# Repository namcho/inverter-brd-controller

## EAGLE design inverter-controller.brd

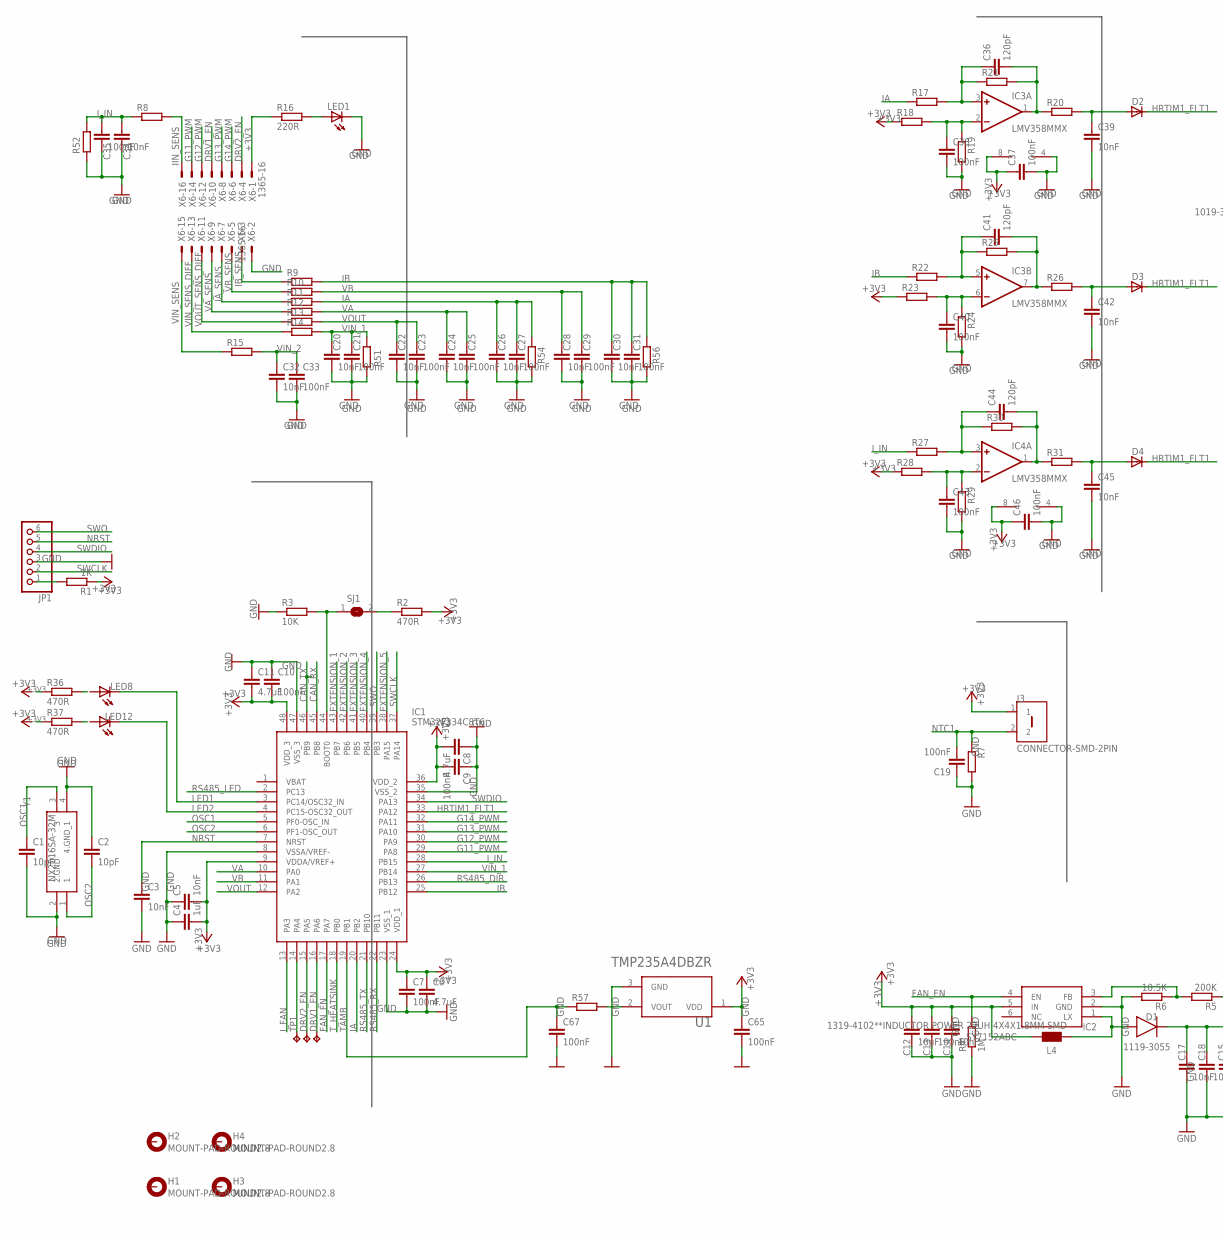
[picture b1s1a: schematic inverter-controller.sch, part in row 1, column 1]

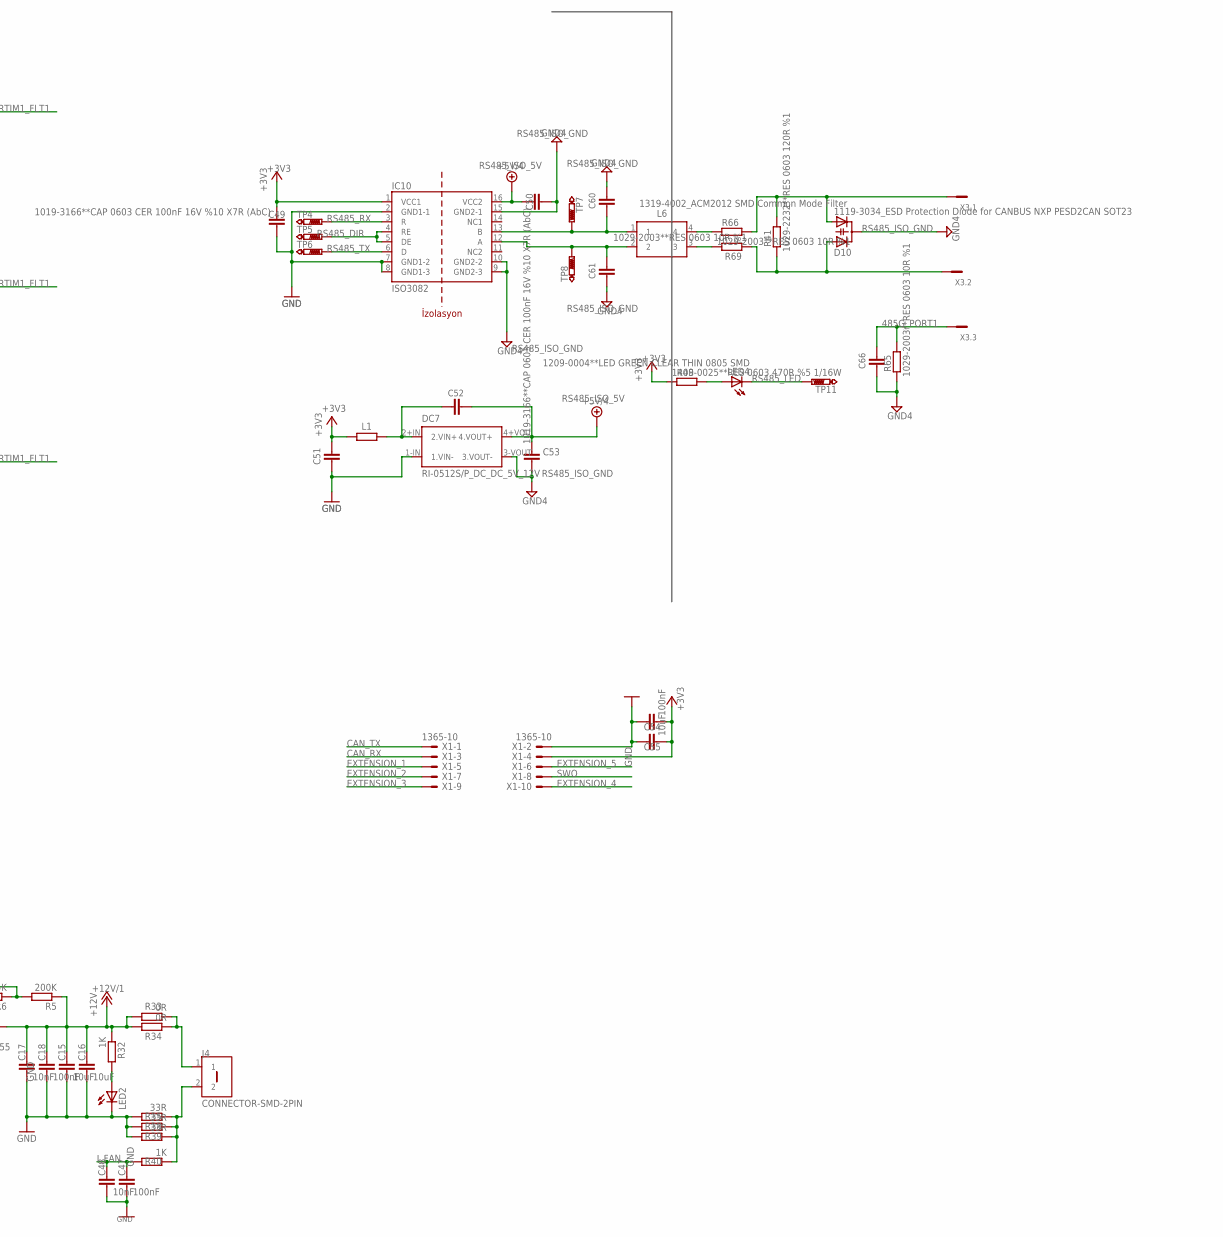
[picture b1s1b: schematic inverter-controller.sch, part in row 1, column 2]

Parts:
C1, C2: 10pF; C0603_ENKO
C3, C5, C14, C17, C20, C22, C24, C26, C28, C30, C32, C34, C39, C42, C45, C48: 10nF; C0603_ENKO
C4: 1uF; C0603_ENKO
C6, C8, C11: 4.7uF; C0603_ENKO
C7, C9, C10, C13, C18, C19, C21, C23, C25, C27, C29, C31, C33, C35, C37, C38, C40, C43, C46, C47, C54, C65, C67: 100nF; C0603_ENKO
C12, C15, C16, C55: 10uF; C0603_ENKO
C36, C41, C44: 120pF; C0603_ENKO
C49, C50: 1019-3166**CAP 0603 CER 100nF 16V %10 X7R (AbC); C0603
C51, C53: 1019-3168","CAP 0805 CER 2.2uF 16V %10 X7R (AbC); C0805
C52: 0019-3020","CAP TH CER 470pF 3kV Y5P %10 85C F=7.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; C050-055X075
C60, C61: 1200920378**CAP 0603 CER 100p 50V%5 NP0; C0603
C66: NC; C0603
D1: 1119-3055; DIOM5226X290N
D2, D3, D4: DIODE-SOD80C; SOD80C
D10: 1119-3034_ESD Protection Diode for CANBUS NXP PES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; SOT23
DC7: RI-0512S/P_DC_DC_5V_12V
H1, H2, H3, H4: MOUNT-PAD-ROUND2.8; 2,8-PAD
IC1: STM32F334C8T6; QFP50P900X900X160-48N
IC2: SY7152ABC; SOT95P285X140-6N
IC3, IC4: LMV358MMX; MSOP08
IC10: ISO3082
J3, J4: CONNECTOR-SMD-2PIN
JP1: PINHD-1X6; 1X06
L1: 1319-4025","INDUCTOR SMD 0805 4.7uH 500mA CL2012C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; R0805
L4: 1319-4102**INDUCTOR POWER 22UH 4X4X1.8MM SMD; WE-PD2_S
L6: 1319-4002_ACM2012 SMD Common Mode Filter; ACM2012-900--2P-T002
LED1, LED2: LEDCHIP-LED0805; CHIP-LED0805
LED4: 1209-0004**LED GREEN CLEAR THIN 0805 SMD; CHIP-LED0805
LED8, LED12: LEDCHIPLED_0805; CHIPLED_0805
R1, R32, R40: 1K; R0603_ENKO
R2, R36, R37: 470R; R0603_ENKO
R3: 10K; R0603_ENKO
R4: 1M; R0603_ENKO
R5: 200K; R0603_ENKO
R6: 10.5K; R0603_ENKO
R7, R8, R9, R10, R11, R12, R13, R14, R15, R17, R18, R19, R20, R21, R22, R23, R24, R25, R26, R27, R28, R29, R30, R31, R51, R52, R54, R56, R57: R-EU_R0603E; R0603_ENKO
R16: 220R; R0603_ENKO
R33, R34: 0R; R0603_ENKO
R35, R38, R39: 33R; R0603_ENKO
R41: 1029-2232**RES 0603 120R %1; R0603
R48: 1409-0025**RES 0603 470R %5 1/16W; R0603
R65, R66, R69: 1029-2003**RES 0603 10R %1; R0603
SJ1: SJ
TP1, TP2, TP3: TPB1,27; B1,27
TP4, TP5, TP6, TP7, TP8, TP11: PTR1TP18R; TP18R
U1: MCP9701; TEXAS_INSTRUMENTS_TMP235A4DBZR_3
X1: 1365-10
X3: 0289-9068**15EDGVC-3.81-03P-14; MCV3
X6: 1365-16
Y1: NX2016SA-32M

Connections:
485A_PORT: D10.1 (A1), R41.1, R69.1, X3.2
485B_PORT: D10.2 (A2), R41.2, R66.2, X3.1
485G_PORT1: C66.1, R65.2, X3.3
+3V3: C4.2, C5.2, C6.1, C7.1, C8.2, C9.2, C10.2, C11.2, C12.1, C13.1, C14.1, C37.1, C46.1, C49.2, C51.1, C54.2, C55.2, C65.1, IC1.9 (VDDA/VREF+), IC1.24 (VDD_1), IC1.36 (VDD_2), IC1.48 (VDD_3), IC2.5 (IN), IC3.8 (V+), IC4.8 (V+), IC10.1 (VCC1), J3.1, L1.1, L4.1 (2), R1.1, R2.2, R16.1, R18.1, R23.1, R28.1, R36.1, R37.1, R48.1, U1.1 (VDD), X1.4, X6.1
+12V/1: C15.1, C16.1, C17.1, C18.1, D1.1 (C), R5.1, R32.1, R33.2, R34.2
CAN_RX: IC1.45 (PB8), X1.3
CAN_TX: IC1.46 (PB9), X1.1
DRV1_EN: IC1.16 (PA6), TP3.TP, X6.10
DRV2_EN: IC1.15 (PA5), TP2.TP, X6.4
EXTENSION_1: IC1.43 (PB7), X1.5
EXTENSION_2: IC1.42 (PB6), X1.7
EXTENSION_3: IC1.41 (PB5), X1.9
EXTENSION_4: IC1.40 (PB4), X1.10
EXTENSION_5: IC1.38 (PA15), X1.6
FAN_EN: IC1.17 (PA7), IC2.4 (EN), R4.2
G11_PWM: IC1.29 (PA8), X6.14
G12_PWM: IC1.30 (PA9), X6.12
G13_PWM: IC1.31 (PA10), X6.8
G14_PWM: IC1.32 (PA11), X6.6
GND: C1.2, C2.1, C3.2, C4.1, C5.1, C6.2, C7.2, C8.1, C9.1, C10.1, C11.1, C12.2, C13.2, C14.2, C15.2, C16.2, C17.2, C18.2, C19.1, C20.2, C21.2, C22.2, C23.2, C24.2, C25.2, C26.2, C27.2, C28.2, C29.2, C30.2, C31.2, C32.2, C33.2, C34.2, C35.2, C37.2, C38.2, C39.2, C40.2, C42.2, C43.2, C45.2, C46.2, C47.2, C48.2, C49.1, C51.2, C54.1, C55.1, C65.2, C67.2, DC7.1-IN (1.VIN-), IC1.8 (VSSA/VREF-), IC1.23 (VSS_1), IC1.35 (VSS_2), IC1.47 (VSS_3), IC2.2 (GND), IC3.4 (V-), IC4.4 (V-), IC10.2 (GND1-1), IC10.7 (GND1-2), IC10.8 (GND1-3), JP1.3, LED1.C, LED2.C, R3.1, R4.1, R6.2, R7.2, R19.2, R24.2, R29.2, R35.2, R38.2, R39.2, R51.1, R52.1, R54.1, R56.1, U1.3 (GND), X1.2, X6.2, Y1.2 (2.GND), Y1.4 (4.GND_1)
HRTIM1_FLT1: D2.C, D3.C, D4.C, IC1.33 (PA12)
IA: C26.1, C27.1, IC1.20 (PB2), R11.2, R17.1, R54.2
IA_SENS: R11.1, X6.7
IB: C30.1, C31.1, IC1.25 (PB12), R9.2, R22.1, R56.2
IB_SENS: R9.1, X6.3
IIN_SENS: R8.2, X6.16
I_FAN: C47.1, C48.1, IC1.13 (PA3), R40.2
I_IN: C34.1, C35.1, IC1.28 (PB15), R8.1, R27.1, R52.2
LED1: IC1.3 (PC14/OSC32_IN), LED8.C
LED2: IC1.4 (PC15-OSC32_OUT), LED12.C
unnamed: C36.2, IC3.1 (OUT), R20.1, R21.2
unnamed: R2.1, SJ1.2
unnamed: IC1.14 (PA4), TP1.TP
unnamed: IC1.44 (BOOT0), R3.2, SJ1.1
unnamed: C36.1, IC3.3 (+IN), R17.2, R21.1
unnamed: IC2.3 (FB), R5.2, R6.1
unnamed: LED2.A, R32.2
unnamed: J4.2, R35.1, R38.1, R39.1, R40.1
unnamed: D1.2 (A), IC2.1 (LX), L4.2 (1)
unnamed: C39.1, D2.A, R20.2
unnamed: C42.1, D3.A, R26.2
unnamed: C38.1, IC3.2 (-IN), R18.2, R19.1
unnamed: C41.1, IC3.5 (+IN), R22.2, R25.1
unnamed: C44.1, IC4.3 (+IN), R27.2, R30.1
unnamed: C40.1, IC3.6 (-IN), R23.2, R24.1
unnamed: C41.2, IC3.7 (OUT), R25.2, R26.1
unnamed: C45.1, D4.A, R31.2
unnamed: C43.1, IC4.2 (-IN), R28.2, R29.1
unnamed: LED1.A, R16.2
unnamed: C44.2, IC4.1 (OUT), R30.2, R31.1
unnamed: LED4.A, R48.2
unnamed: JP1.1, R1.2
unnamed: J4.1, R33.1, R34.1
unnamed: LED8.A, R36.2
unnamed: C61.1, IC10.12 (A), L6.2, TP8.TP
unnamed: L6.4, R66.1
unnamed: R57.2, U1.2 (VOUT)
unnamed: LED12.A, R37.2
unnamed: L6.3, R69.2
unnamed: C60.2, IC10.13 (B), L6.1, TP7.TP
unnamed: C52.1, DC7.2+IN (2.VIN+), L1.2
NRST: C3.1, IC1.7 (NRST), JP1.5
NTC1: C19.2, J3.2, R7.1
OSC1: C1.1, IC1.5 (PF0-OSC_IN), Y1.3
OSC2: C2.2, IC1.6 (PF1-OSC_OUT), Y1.1
RS485_DIR: IC1.26 (PB13), IC10.4 (RE), IC10.5 (DE), TP5.TP
RS485_ISO_5V: C50.2, C52.2, C53.1, DC7.4+VOU (4.VOUT+), IC10.16 (VCC2)
RS485_ISO_GND: C50.1, C53.2, C60.1, C61.2, C66.2, D10.3 (C), DC7.3-VOUT (3.VOUT-), IC10.9 (GND2-3), IC10.10 (GND2-2), IC10.15 (GND2-1), R65.1
RS485_LED: IC1.2 (PC13), LED4.C, TP11.TP
RS485_RX: IC1.22 (PB11), IC10.3 (R), TP4.TP
RS485_TX: IC1.21 (PB10), IC10.6 (D), TP6.TP
SWCLK: IC1.37 (PA14), JP1.2
SWDIO: IC1.34 (PA13), JP1.4
SWO: IC1.39 (PB3), JP1.6, X1.8
TAMB: C67.1, IC1.19 (PB1), R57.1
T_HEATSINK: IC1.18 (PB0)
VA: C24.1, C25.1, IC1.10 (PA0), R12.2
VA_SENS: R12.1, X6.9
VB: C28.1, C29.1, IC1.11 (PA1), R10.2
VB_SENS: R10.1, X6.5
VIN_1: C20.1, C21.1, IC1.27 (PB14), R14.2, R51.2
VIN_2: C32.1, C33.1, R15.2
VIN_SENS: R15.1, X6.15
VIN_SENS_DIFF: R14.1, X6.13
VOUT: C22.1, C23.1, IC1.12 (PA2), R13.2
VOUT_SENS_DIFF: R13.1, X6.11

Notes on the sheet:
İzolasyon

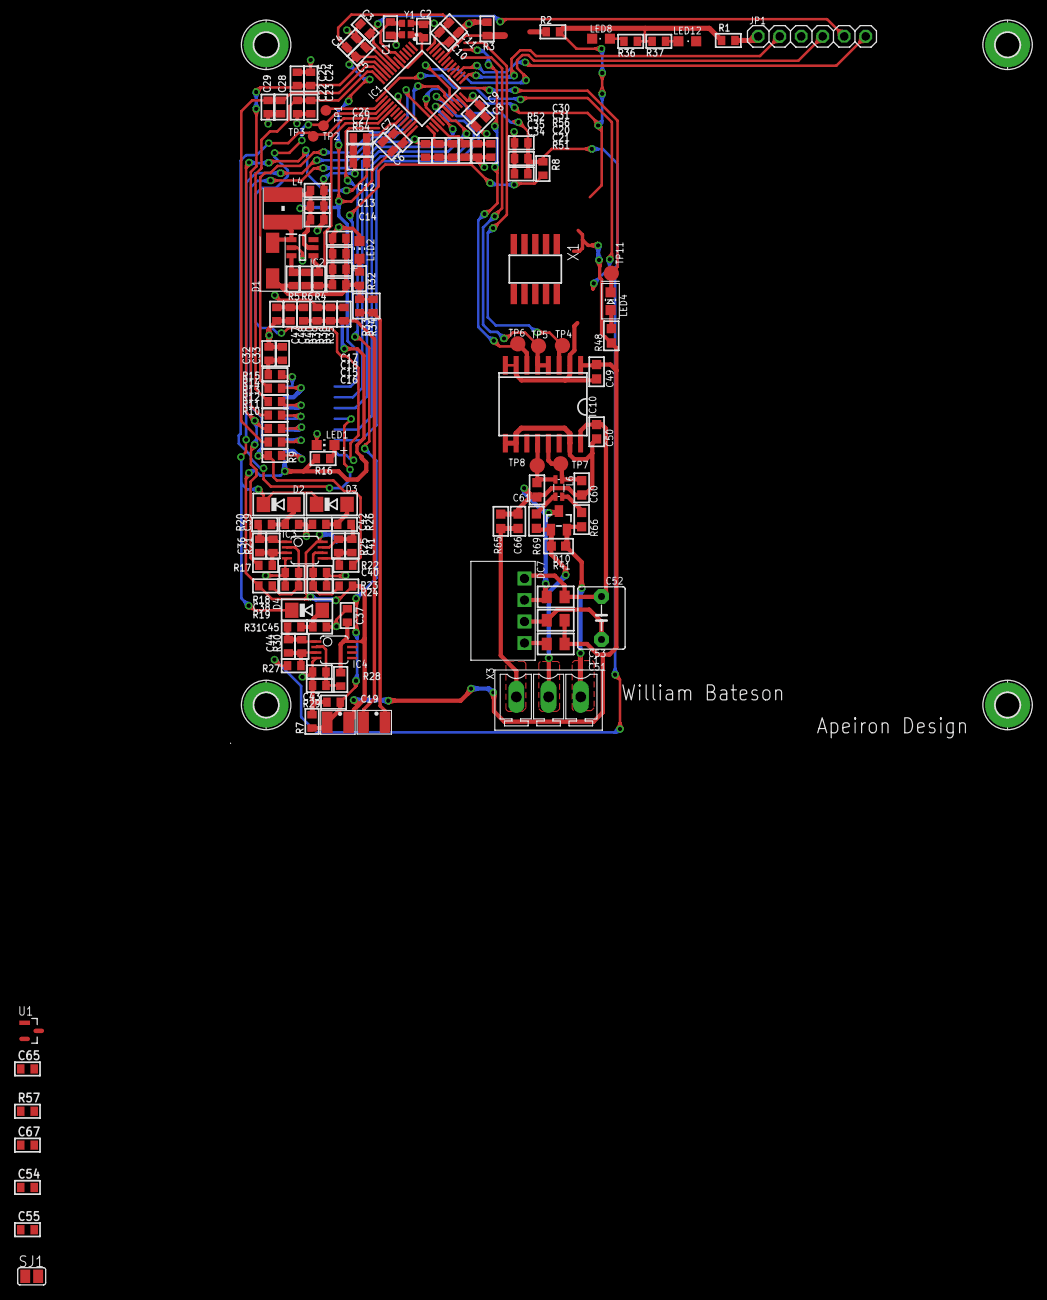
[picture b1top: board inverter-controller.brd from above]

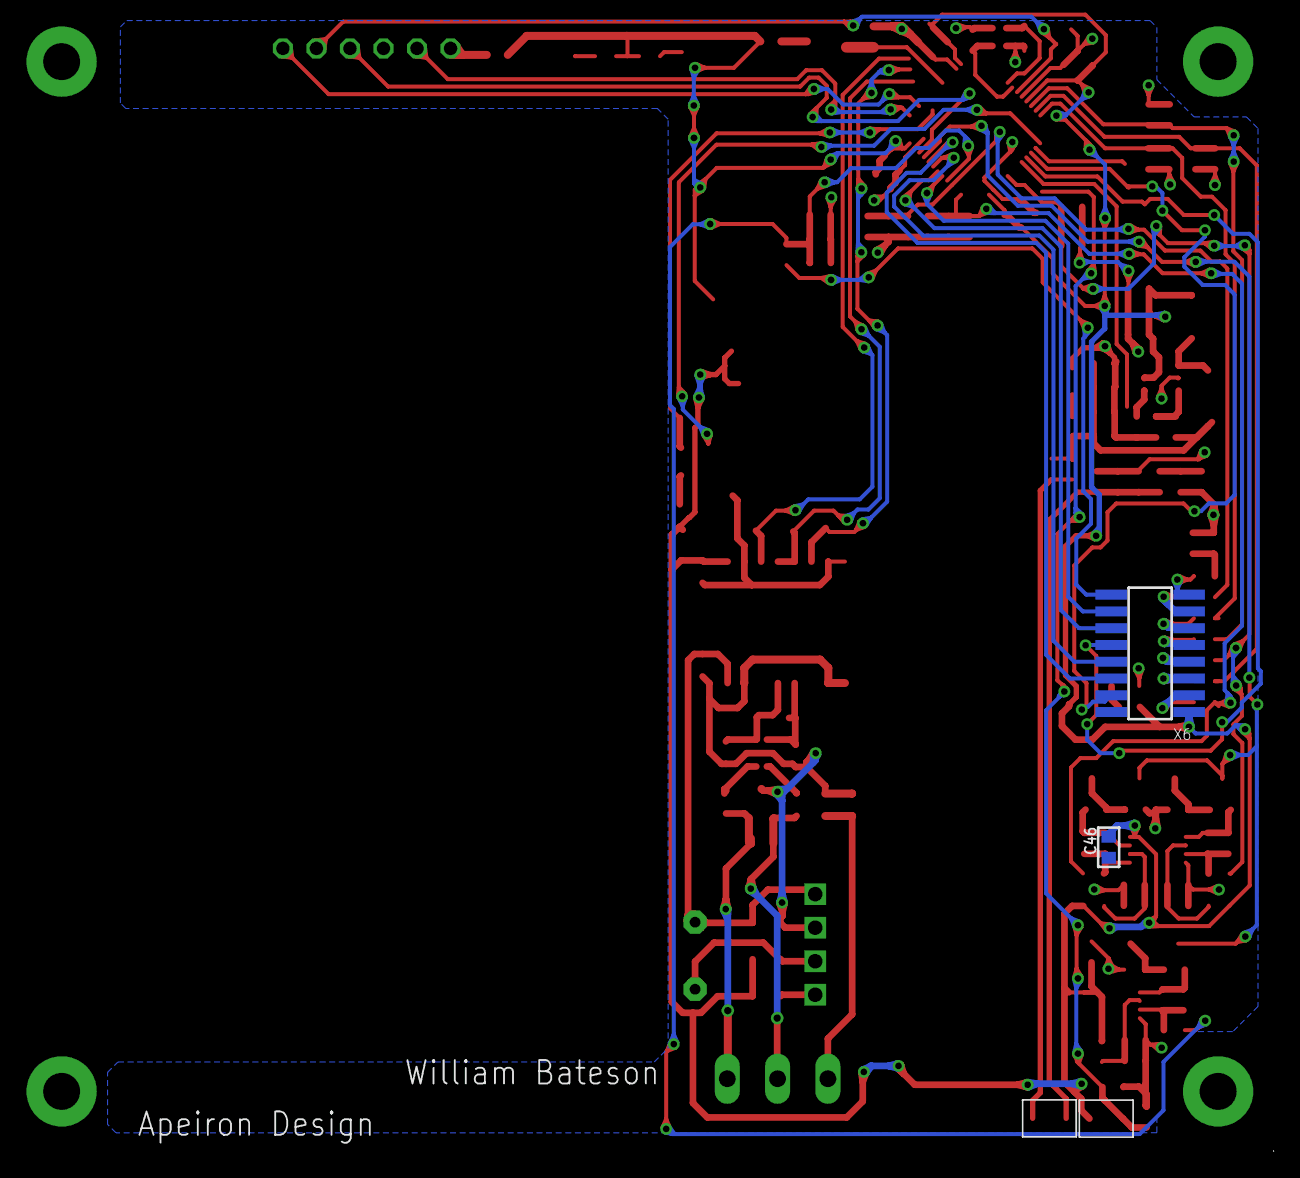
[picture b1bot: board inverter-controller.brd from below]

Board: 3 copper layers, 151 parts (2 on the bottom side), 85 nets.

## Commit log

2021-04-21 inverter icin kontrol karti semasi cizildi.
2021-04-21 Relay soketleri eklendi.
2021-06-14 .s# ve .b# dosya takipleri engellendi.
2021-06-14 Mekanik kistaslar belirlendi.
2021-06-14 Mini kart tasarimi icin sadelestirildi.
2021-06-14 DXF yuklendi
2021-06-14 Direnc ve kondansator kutuphaneleri degistirildi(silk sorunu nedeniyle).
2021-06-14 Akim olcumleri icin gerilim bolucu direncler eklendi.
2021-06-14 Kart boyutu ayarlandi, baglanti soketi yerlesimi yapildi.
2021-06-14 Fan beslemelerinden bir tanesi silindi.
2021-06-14 RS485 eklendi.
2021-06-14 RS485 DC-DC besleme gerilimi 3V yapildi.
2021-06-14 Programlama soketi baglantilari duzeltildi.
2021-06-14 RS485 DC-DC paketi degistirildi.
2021-06-14 Fan ve NTC soketleri SMD-Pad kutuphanesi ile degistirildi.
2021-06-14 Board icin maksimum genisleme alani cizildi.
2021-06-14 Tum koselerdeki hole'lerden destek alinabilecek sekilde kart boyutlari duzenlendi.
2021-06-14 485 pinleri degistirildi, analog-girisler icin aciklama eklendi.
2021-06-16 Opamp devreleri düzenlendi.
2021-06-16 Dxf dosyasi cizimin uzerine eklendi, kart boyutlarinda duzenleme yapildi.
2021-06-16 Kart baglanti pad'leri eklendi.
2021-06-17 RC Filtreleri ve Decoupling Cap. yerleştirildi.
2021-06-17 Fan Controller-2 yerleşimi yapıldı
2021-06-18 Programlama soketi degistirildi.
2021-06-18 Kartin alt kismindaki PCB baglanti bolgesi ust bolge ile simetrik yapildi.
2021-06-18 Layout tamamlandı
2021-06-18 DRC Kontrolleri yapıldı Teardrops yapıldı.
2021-06-18 Name silk düzenlendi.
2021-06-23 Fan beslemelerinden 1 tanesi silindi, genisleme karti icin soket eklendi.
2021-06-23 Ana kart baglanti soketindeki GND baglanti sorunu giderildi(ERC).
2021-06-23 NTC1 net ismi T_HEATSINK yapildi.

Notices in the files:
parts and their libraries:
wuerth-elektronik: Copyright: Würth Elektronik eiSos
